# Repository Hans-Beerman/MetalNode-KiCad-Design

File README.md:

**MetalNode MakerSpace Leiden**

The MetalNode is used to control the access to the Abene and the Stationary Large Grinder of the MakerSpace in Leiden

This repository contains the schematic drawings, made in KiCad for this node.

The PCB in this design is not meant to be used for a real printed circuit board, but is added to be used as a guideline for making the print by hand on a prefab PCB for experimental use.

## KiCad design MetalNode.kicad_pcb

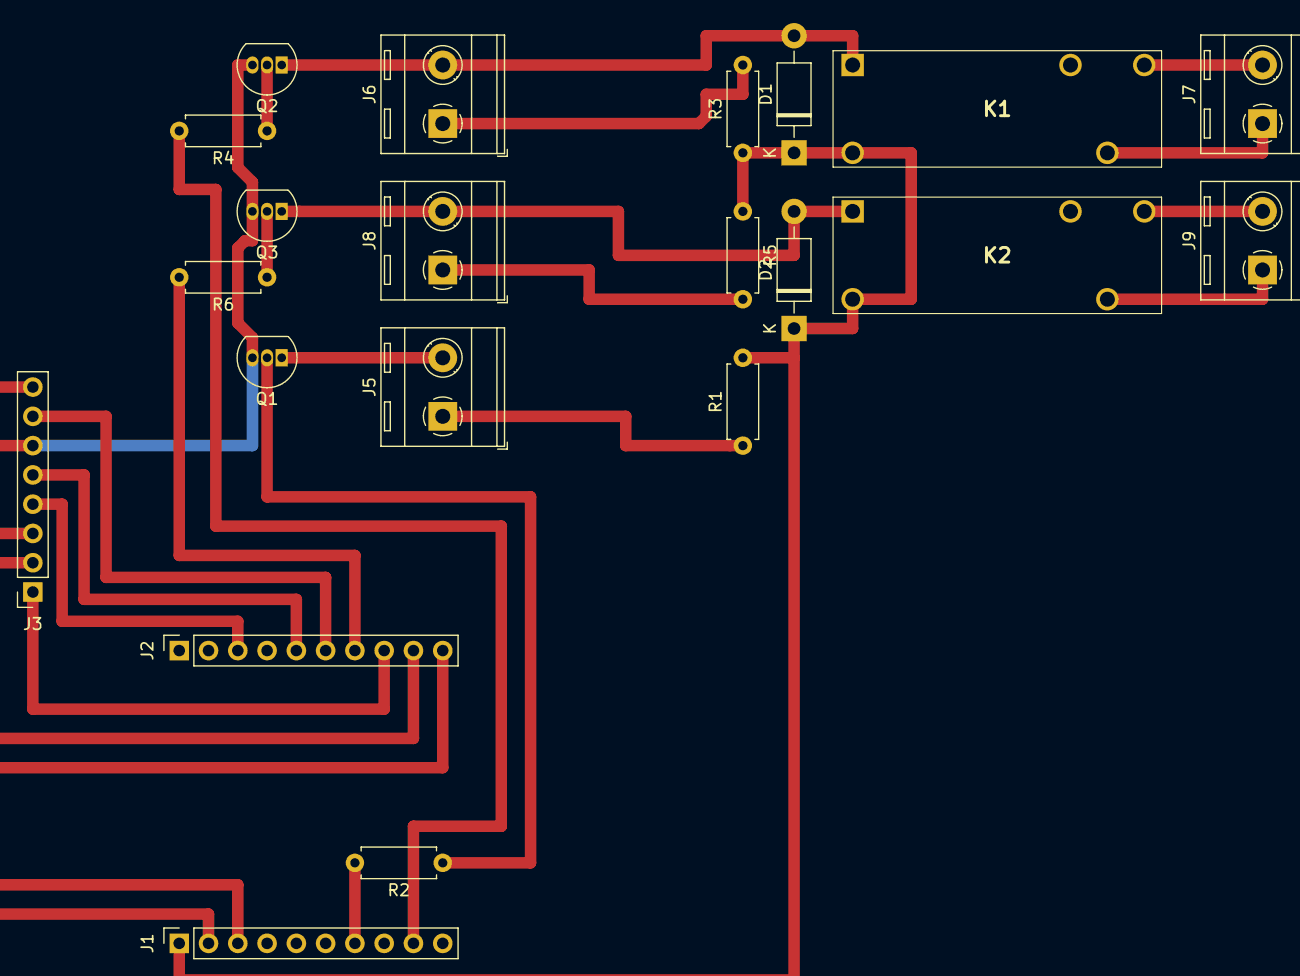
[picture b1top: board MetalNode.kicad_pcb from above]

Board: 2 copper layers, 21 parts (0 on the bottom side), 25 nets.

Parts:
D1, D2: 1N4007; D_DO-41_SOD81_P10.16mm_Horizontal
J1: EXT1; PinSocket_1x10_P2.54mm_Vertical
J2: EXT2; PinSocket_1x10_P2.54mm_Vertical
J3: Conn_01x08; PinSocket_1x08_P2.54mm_Vertical
J5, J6, J7, J8, J9: Screw_Terminal_01x02; TerminalBlock_RND_205-00287_1x02_P5.08mm_Horizontal
K1, K2: HF118F_005-1ZS1T_136_; HF118F0051ZS1T136
Q1, Q2, Q3: BC547; TO-92_Inline
R1, R2, R3, R4, R5, R6: 1k; R_Axial_DIN0207_L6.3mm_D2.5mm_P7.62mm_Horizontal

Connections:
3V3: J1.2, J3.8
+5V: D1.1, D2.1, J1.1, K1.2, K2.2, R1.2, R3.1, R5.1
GND: J1.3, J3.6, Q1.3, Q2.3, Q3.3
GPI35: J2.3, J3.4
GPIO2_HS2_DATA0: J1.7, R2.2
GPIO4_U1TXD: J1.9, R4.2
GPIO13_I2C-SDA: J2.10, J3.3
GPIO14_HS2_CLK: J2.9, J3.2
GPIO15_HS2_CMD: J2.8, J3.1
GPIO16_I2C-SCL: J2.7, R6.2
GPIO32: J2.6, J3.7
GPIO33: J2.5, J3.5
unnamed: D1.2, J6.2, K1.1, Q2.1
unnamed: D2.2, J8.2, K2.1, Q3.1
unnamed: J5.1, R1.1
unnamed: J5.2, Q1.1
unnamed: J6.1, R3.2
unnamed: J7.1, K1.3
unnamed: J7.2, K1.4
unnamed: J8.1, R5.2
unnamed: J9.1, K2.3
unnamed: J9.2, K2.4
unnamed: Q1.2, R2.1
unnamed: Q2.2, R4.1
unnamed: Q3.2, R6.1

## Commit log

2020-07-09 V0.1 first release
2020-07-09 V0.1 README.md and LICENSE file added
